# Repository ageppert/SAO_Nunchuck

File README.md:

# SAO NUNCHUCK

Easily connect a Wii Nunchuck to your Badge or project with an SAO port.

Follow this project at: https://hackaday.io/project/198000-sao-nunchuck

Libraries to access the features: 

https://github.com/madhephaestus/WiiChuck/

https://github.com/dmadison/NintendoExtensionCtrl

Hardware Version 1.0

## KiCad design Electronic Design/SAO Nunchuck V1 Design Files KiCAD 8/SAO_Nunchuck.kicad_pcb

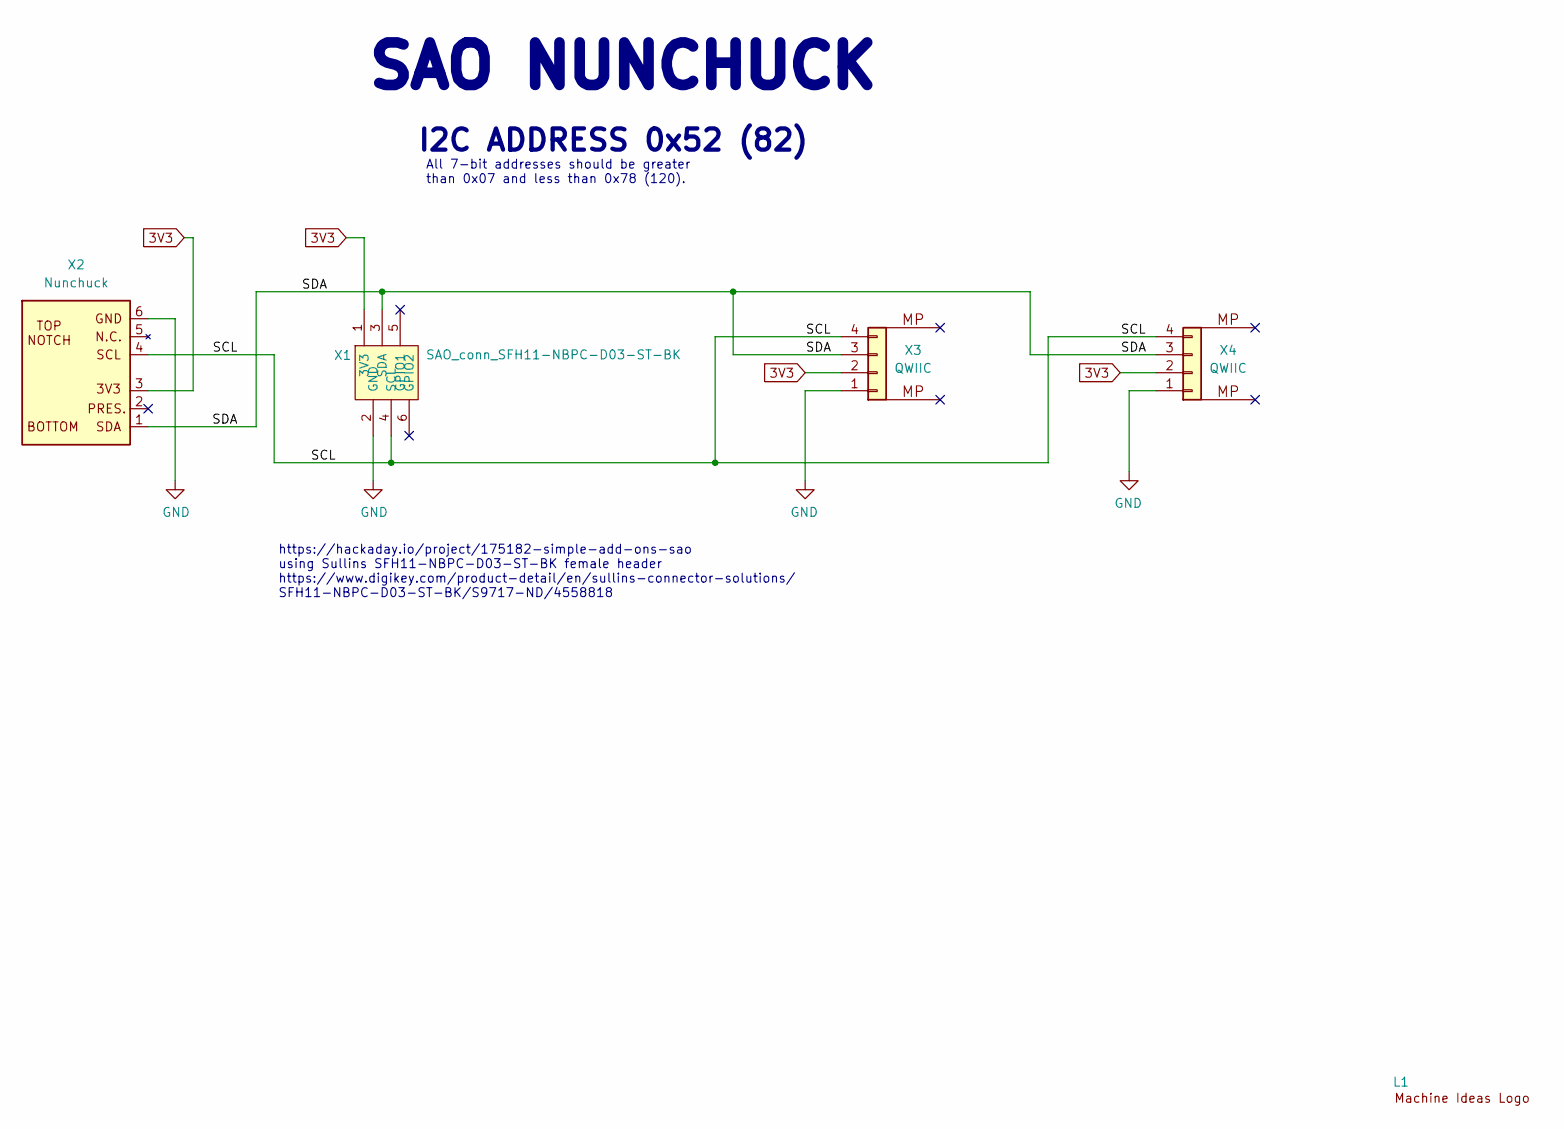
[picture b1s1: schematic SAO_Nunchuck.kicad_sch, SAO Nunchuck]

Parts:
L1: Machine_Ideas_logo
X1: SAO_conn_SFH11-NBPC-D03-ST-BK; Badgelife-SAOv169-BADGE-2x3-Edge-Connect-no-front-text; MPN SFH11-NBPC-D03-ST-BK
X2: Nunchuck; Nunchuk-male
X3: QWIIC; JST_SH_SM04B-SRSS-TB_1x04-1MP_P1.00mm_Horizontal; MPN SM04B-SRSS-TB; LCSC C160404
X4: QWIIC; JST_SH_SM04B-SRSS-TB_1x04-1MP_P1.00mm_Horizontal_QWIIC; MPN SM04B-SRSS-TB; LCSC C160404

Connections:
3V3: X1.1 (3V3), X2.3, X3.2, X4.2
/SCL: X1.4 (SCL), X2.4, X3.4, X4.4
/SDA: X1.3 (SDA), X2.1, X3.3, X4.3
GND: X1.2 (GND), X2.6, X3.1, X4.1

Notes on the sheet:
https://hackaday.io/project/175182-simple-add-ons-sao using Sullins SFH11-NBPC-D03-ST-BK female header https://www.digikey.com/product-detail/en/sullins-connector-solutions/ SFH11-NBPC-D03-ST-BK/S9717-ND/4558818
I2C ADDRESS 0x52 (82)
SAO NUNCHUCK
All 7-bit addresses should be greater than 0x07 and less than 0x78 (120).

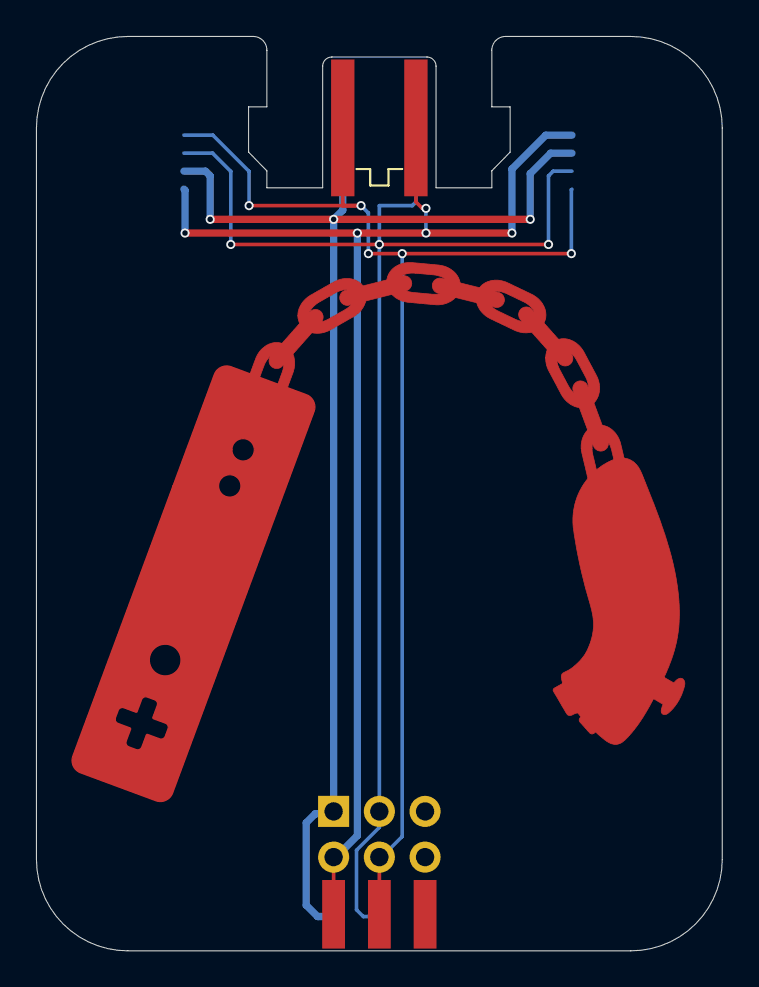
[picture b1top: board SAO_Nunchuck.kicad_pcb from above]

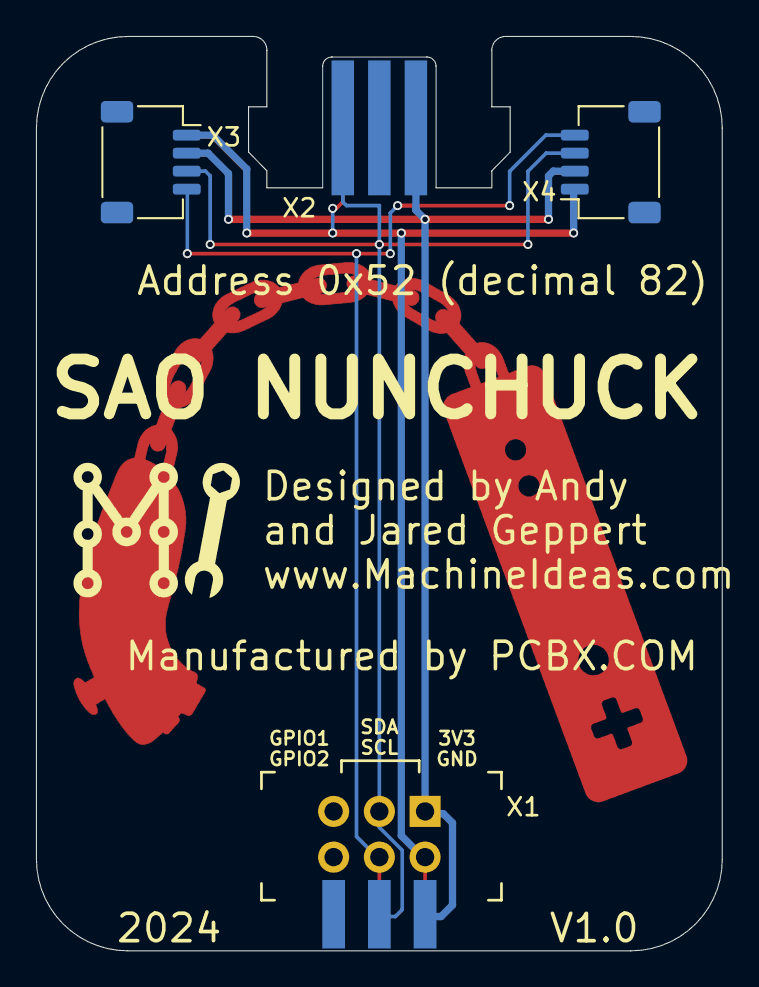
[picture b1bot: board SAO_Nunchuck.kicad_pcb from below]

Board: 2 copper layers, 38.1 x 50.8 mm, 5 parts (3 on the bottom side), 4 nets.

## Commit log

2024-10-14 Add schematic V1
2024-10-14 Add WIP demo firmware
2024-10-18 Add another library link
